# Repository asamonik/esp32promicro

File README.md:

# !!UNTESTED!! ESP32-S3 pro micro dev board

currently waiting for boards

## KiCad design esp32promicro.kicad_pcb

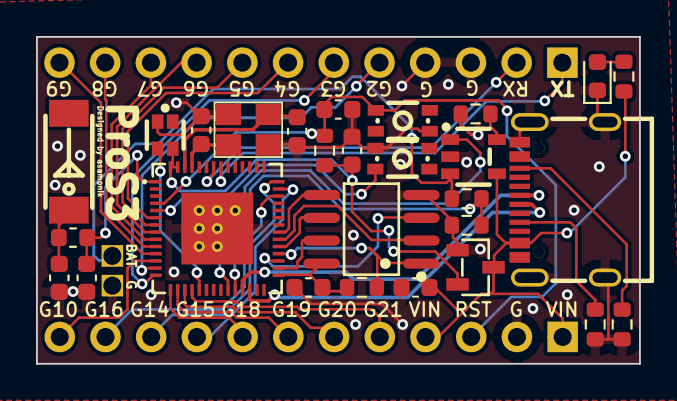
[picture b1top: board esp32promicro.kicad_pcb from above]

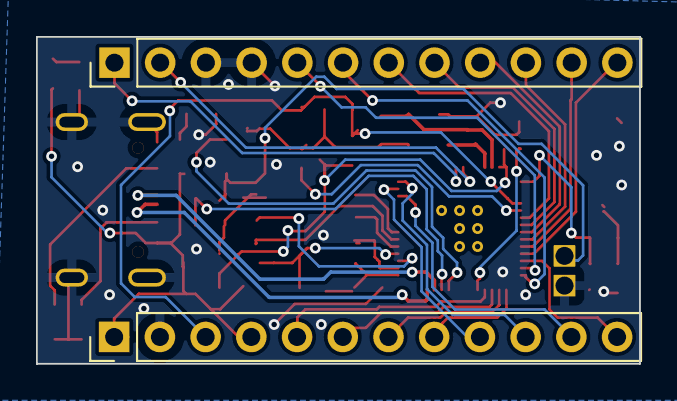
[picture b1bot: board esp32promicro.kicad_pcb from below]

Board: 2 copper layers, 33.5 x 18.2 mm, 32 parts (2 on the bottom side), 44 nets.

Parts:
C1, C2: 1u; C_0603_1608Metric
C3, C4, C5, C6, C7, C8: C; C_0603_1608Metric
CRYSTAL1: CF4040M00008001; CRYSTAL-SMD_4P-L3.2-W2.5-BL_SIT8008BI
D1: LED; LED_0603_1608Metric
J1, J2: Conn_01x12_Pin; PinHeader_1x12_P2.54mm_Vertical
J3, J4: Conn_01x01_Pin; PinHeader_1x01_P2.54mm_Vertical
L1: AN2051-245; ANT2051
L2: L; L_0603_1608Metric
LED1: XL-1615RGBC-WS2812B; LED-SMD_4P-L1.6-W1.5_XL-1615RGBC-WS2812B
R1, R2: 5k1; R_0603_1608Metric
R3, R4, R5, R6, R7, R9: R; R_0603_1608Metric
SW1, SW3: 1TS028A-1300-0600-CT; SW-SMD_4P-L2.8-W1.9-P1.20-LS3.0_1TS028A
U1: ESP32-S3; QFN-56_L7.0-W7.0-P0.40-TL-EP4.0
U2: GD25Q80CTIGR; SOP-8_L5.0-W4.0-P1.27-LS6.0-BL
U3: XC6206P332MR_C5148692; SOT-23-3_L2.9-W1.3-P1.90-LS2.4-BR
U4: GT-USB-7010AN; USB-SMD_GT-USB-7010AN
U5: TP4065; SOT-23-5_L3.0-W1.7-P0.95-LS2.8-BR

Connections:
4: J1.7, U1.6 (GPIO1)
5: J1.8, U1.7 (GPIO2)
6: J1.9, U1.8 (GPIO3)
7: J1.10, U1.9 (GPIO4)
8: J1.11, U1.10 (GPIO5)
9: J1.12, U1.11 (GPIO6)
10: J2.12, U1.12 (GPIO7)
18: J2.8, U1.15 (GPIO10)
19: J2.7, U1.16 (GPIO11)
20: J2.6, U1.17 (GPIO12)
21: J2.5, U1.18 (GPIO13)
+3V3: C2.1, LED1.2 (VDD), R4.1, U1.55 (VDDA), U1.56 (VDDA), U3.2 (VOUT)
+5V: C1.1, J2.1, J2.4, R3.1, U3.3 (VIN), U4.A4B9 (VBUS), U5.4 (VCC)
+BATT: J3.1, R6.1, U5.3 (BAT)
ANTENNA: C8.1, L2.1, U1.1 (LNA_IN)
CHRG: U1.23 (GPIO17), U5.1 (CHRG)
GND: C1.2, C2.2, C3.2, C4.1, C5.2, C6.1, C7.2, C8.2, CRYSTAL1.2 (GND), CRYSTAL1.4 (GND), D1.1 (K), J1.3, J1.4, J2.2, J4.1, LED1.3 (GND), R1.2, R2.2, R7.2, R9.2, SW1.1, SW3.1, U1.57 (EP), U2.4 (VSS), U3.1 (VSS), U4.13 (GND), U4.14 (GND), U4.15 (GND), U4.16 (GND), U4.B1A12 (GND), U5.2 (GND)
IO0: SW3.2, U1.5 (GPIO0)
MISO14: J2.10, U1.42 (GPIO37)
MOSI16: J2.11, U1.40 (GPIO35)
unnamed: D1.2 (A), R3.2
unnamed: C7.1, L1.1 (ANT), L2.2
unnamed: R2.1, U4.A5 (CC1)
unnamed: R1.1, U4.B5 (CC2)
unnamed: R9.1, U5.5 (PROG)
RESET: C3.1, J2.3, R4.2, SW1.4, U1.4 (CHIP_PU)
RGBLED: LED1.4 (DI), U1.19 (GPIO14)
RXD: J1.2, U1.50 (U0RXD)
SCL3: J1.6, U1.14 (GPIO9)
SCLK15: J2.9, U1.41 (GPIO36)
SDA2: J1.5, U1.13 (GPIO8)
SPICLK: U1.33 (SPICLK), U2.6 (SCLK)
SPICS: R5.2, U1.32 (SPICS0), U2.1 (~CS)
SPID: U1.35 (SPID), U2.5 (SI(IO0))
SPIHD: U1.30 (SPIHD), U2.7 (HOLD#(IO3))
SPIQ: U1.34 (SPIQ), U2.2 (SO(IO1))
SPIWP: U1.31 (SPIWP), U2.3 (WP#(IO2))
TXD: J1.1, U1.49 (U0TXD)
USBN: U1.25 (GPIO19), U4.A7 (DN1)
USBP: U1.26 (GPIO20), U4.A6 (DP1)
VBAT: R6.2, R7.1, U1.24 (GPIO18)
VDDSPI: C6.2, R5.1, U1.29 (VDD_SPI), U2.8 (VCC)
XTALN: C5.1, CRYSTAL1.3, U1.53 (XTAL_N)
XTALP: C4.2, CRYSTAL1.1, U1.54 (XTAL_P)

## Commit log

2024-02-05 init
